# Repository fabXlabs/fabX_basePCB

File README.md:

# fabX_basePCB
Alterantive M5Stack Bottom for fabX with headers to interface with expansion boards

# This pcb is not tested yet

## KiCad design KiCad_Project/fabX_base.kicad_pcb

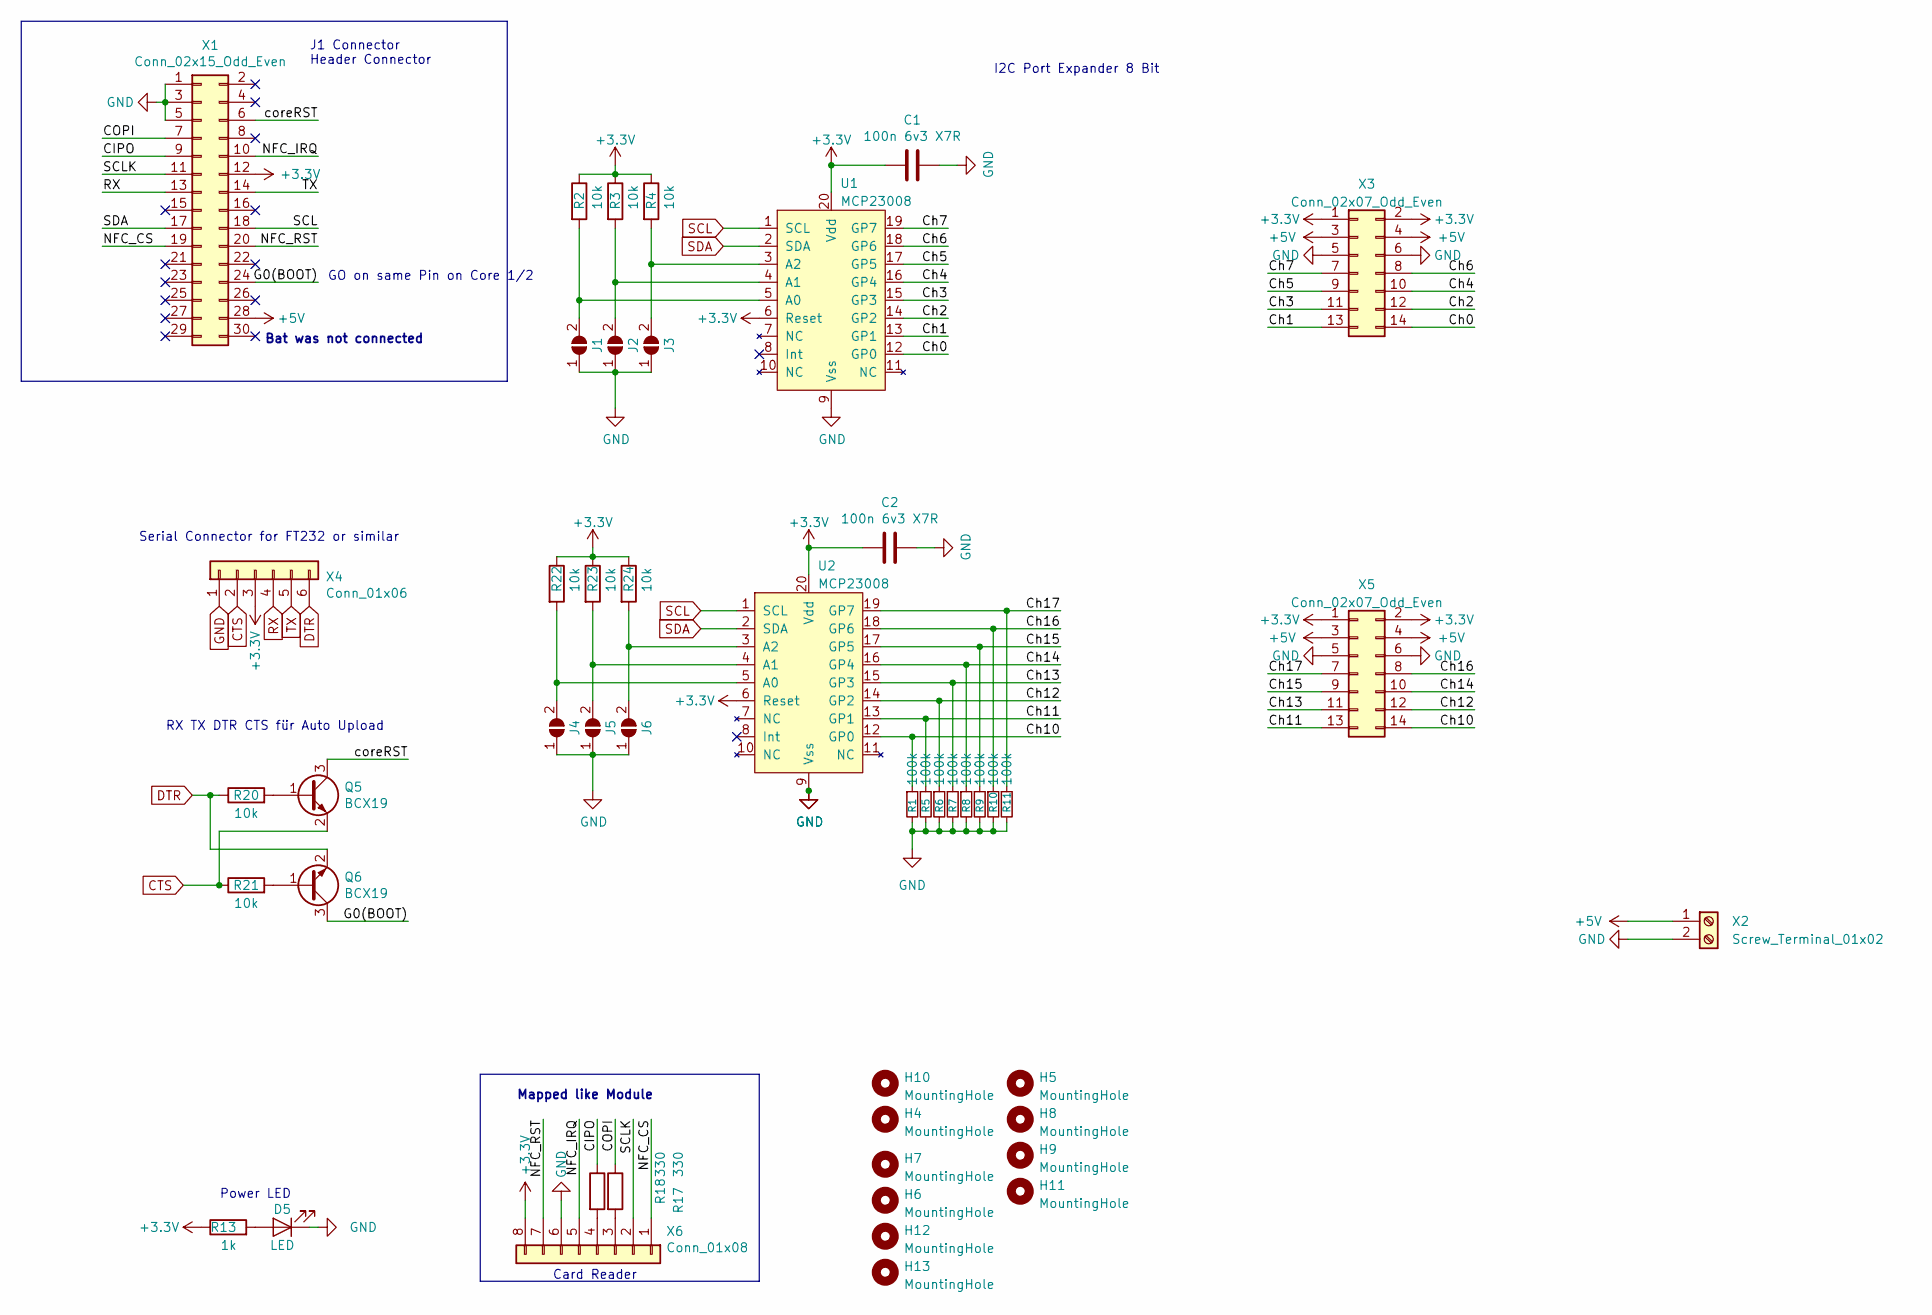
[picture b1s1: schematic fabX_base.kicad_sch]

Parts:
C1, C2: 100n 6v3 X7R; C_0603_1608Metric; Farnell# 3345771
D5: LED; LED_0603_1608Metric; Farnell# 2099257
H4, H6, H7, H10, H12, H13: MountingHole; MountingHole_3.2mm_M3_noSolder
H5, H8, H9, H11: MountingHole; MountingHole_3.2mm_M3_noSolderCorner
J1, J2, J3, J4, J5, J6: SolderJumper_2_Open; SolderJumper-2_P1.3mm_Open_RoundedPad1.0x1.5mm
Q5, Q6: BCX19; SOT-23; Farnell# 2317581
R1, R5, R6, R7, R8, R9, R10, R11: 100k; R_0603_1608Metric
R2, R3, R4, R20, R21, R22, R23, R24: 10k; R_0603_1608Metric; Farnell# 3495224
R13: 1k; R_0603_1608Metric; Farnell# 3495238
R17, R18: 330; R_0603_1608Metric; Farnell# 3950907
U1, U2: MCP23008; SSOP-20_5.3x7.2mm_P0.65mm; Farnell# 1605564
X1: Conn_02x15_Odd_Even; PinSocket_2x15_P2.54mm_Vertical
X2: Screw_Terminal_01x02; PhoenixContact_MSTBA_2,5_2-G-5,08_1x02_P5.08mm_Horizontal
X3, X5: Conn_02x07_Odd_Even; IDC-Header_2x07_P2.54mm_Horizontal; Farnell# 2356264
X4: Conn_01x06; PinSocket_1x06_P2.54mm_Vertical; Farnell# 2084276
X6: Conn_01x08; PinSocket_1x08_P2.54mm_Horizontal

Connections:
+3V3: C1.2, C2.2, R2.1, R3.1, R4.1, R13.1, R22.1, R23.1, R24.1, U1.6 (Reset), U1.20 (Vdd), U2.6 (Reset), U2.20 (Vdd), X1.12, X3.1, X3.2, X4.3, X5.1, X5.2, X6.8
+5V: X1.28, X2.1, X3.3, X3.4, X5.3, X5.4
/CIPO: R18.1, X1.9
/COPI: R17.1, X1.7
/Ch0: U1.12 (GP0), X3.14
/Ch1: U1.13 (GP1), X3.13
/Ch2: U1.14 (GP2), X3.12
/Ch3: U1.15 (GP3), X3.11
/Ch4: U1.16 (GP4), X3.10
/Ch5: U1.17 (GP5), X3.9
/Ch6: U1.18 (GP6), X3.8
/Ch7: U1.19 (GP7), X3.7
/Ch10: R1.1, U2.12 (GP0), X5.14
/Ch11: R5.1, U2.13 (GP1), X5.13
/Ch12: R6.1, U2.14 (GP2), X5.12
/Ch13: R7.1, U2.15 (GP3), X5.11
/Ch14: R8.1, U2.16 (GP4), X5.10
/Ch15: R9.1, U2.17 (GP5), X5.9
/Ch16: R10.1, U2.18 (GP6), X5.8
/Ch17: R11.1, U2.19 (GP7), X5.7
/G0(BOOT): Q6.3 (C), X1.24
/NFC_CS: X1.19, X6.1
/NFC_IRQ: X1.10, X6.5
/NFC_RST: X1.20, X6.7
/SCLK: X1.11, X6.2
/coreRST: Q5.3 (C), X1.6
CTS: Q5.2 (E), R21.1, X4.2
DTR: Q6.2 (E), R20.1, X4.6
GND: C1.1, C2.1, D5.1 (K), J1.1 (A), J2.1 (A), J3.1 (A), J4.1 (A), J5.1 (A), J6.1 (A), R1.2, R5.2, R6.2, R7.2, R8.2, R9.2, R10.2, R11.2, U1.9 (Vss), U2.9 (Vss), X1.1, X1.3, X1.5, X2.2, X3.5, X3.6, X4.1, X5.5, X5.6, X6.6
unnamed: D5.2 (A), R13.2
unnamed: J1.2 (B), R2.2, U1.5 (A0)
unnamed: J2.2 (B), R3.2, U1.4 (A1)
unnamed: J3.2 (B), R4.2, U1.3 (A2)
unnamed: J4.2 (B), R22.2, U2.5 (A0)
unnamed: J5.2 (B), R23.2, U2.4 (A1)
unnamed: J6.2 (B), R24.2, U2.3 (A2)
unnamed: Q5.1 (B), R20.2
unnamed: Q6.1 (B), R21.2
unnamed: R17.2, X6.3
unnamed: R18.2, X6.4
RX: X1.13, X4.4
SCL: U1.1 (SCL), U2.1 (SCL), X1.18
SDA: U1.2 (SDA), U2.2 (SDA), X1.17
TX: X1.14, X4.5

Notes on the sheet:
Card Reader
GO on same Pin on Core 1/2
RX TX DTR CTS für Auto Upload
Bat was not connected
Serial Connector for FT232 or similar
J1 Connector Header Connector
Mapped like Module
I2C Port Expander 8 Bit
Power LED

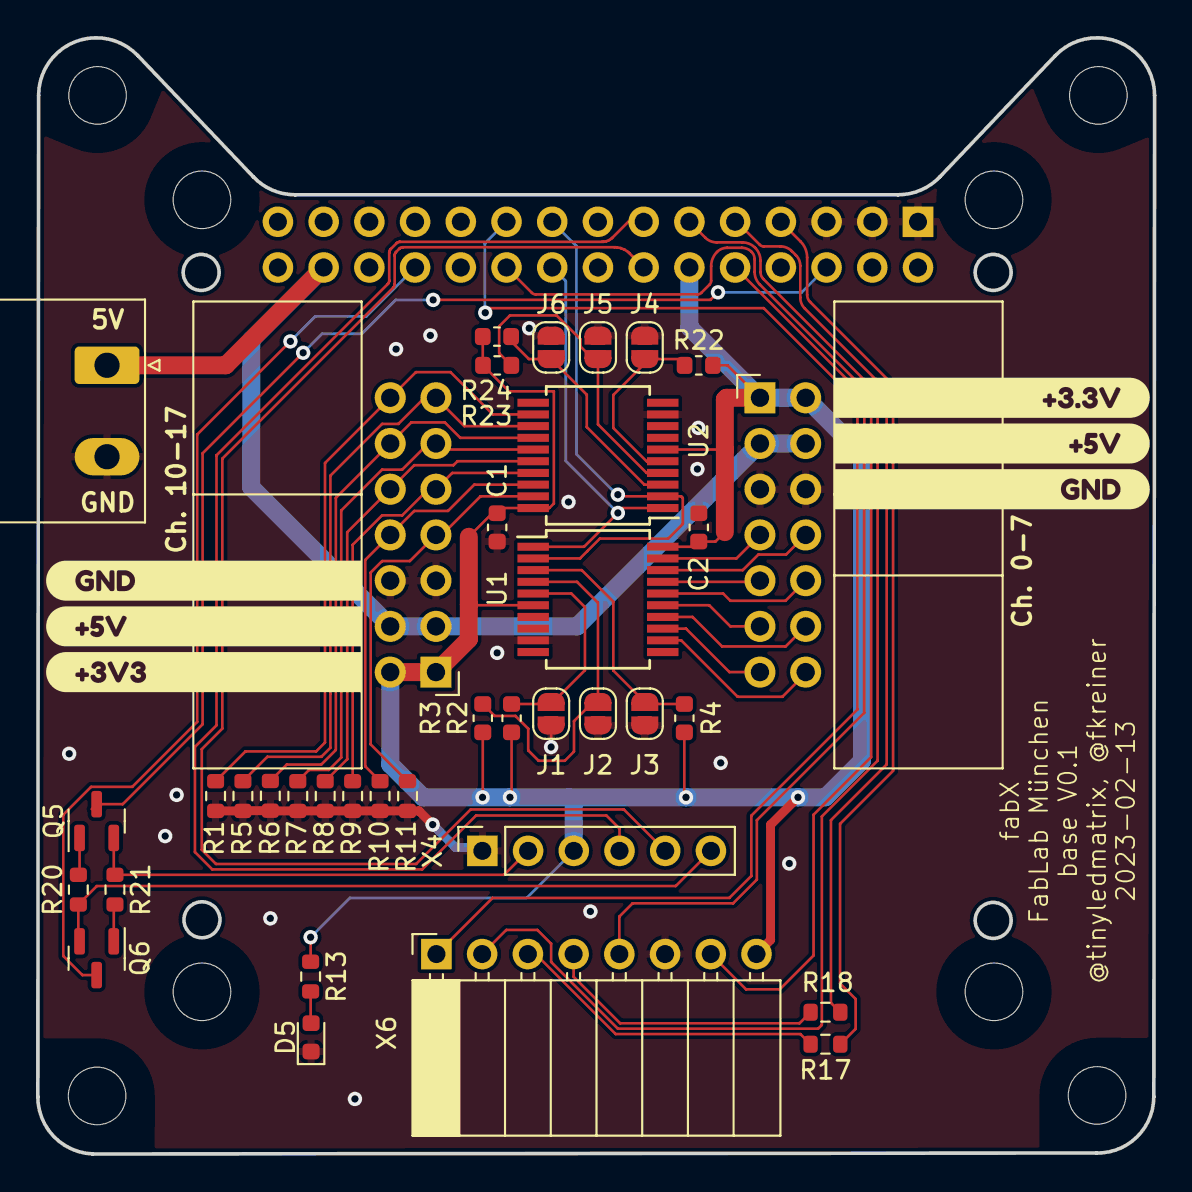
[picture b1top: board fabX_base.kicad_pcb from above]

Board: 2 copper layers, 62.0 x 62.0 mm, 52 parts (1 on the bottom side), 44 nets.

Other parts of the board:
H11#2, H11#3: MountingHole; MountingHole_3.2mm_M3_noSolderCorner
kibuzzard-632A457B: G***; kibuzzard-632A457B
kibuzzard-632A4549: G***; kibuzzard-632A4549
kibuzzard-632A4565: G***; kibuzzard-632A4565
kibuzzard-635FD36E: G***; kibuzzard-635FD36E
kibuzzard-635FD364: G***; kibuzzard-635FD364
kibuzzard-635FD378: G***; kibuzzard-635FD378

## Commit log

2023-08-28 add kicad project
2023-12-12 Create LICENSE
2023-12-29 add pulldowns to inputs
2023-12-29 place pulldowns
